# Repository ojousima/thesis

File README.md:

# Energy Harvester Design for Intelligent Tyre Systems
##TLDR
Modern tyres can have sensor systems which require energy. Currently these 
systems are powered by batteries, which limit the power available and lifetime
of the systems. This study presents an energy harvester system to power such
sensor systems. Piezoelectric and electromagnetic harvester designs are presented
and the piezoelectric harvester design was selected for use in the tyre. Electrical
energy was harvested from tyre rotation and deformation, harvested power was
rectified and stored into a supercapacitor at a voltage level usable by modern
microcontrollers. Tens of milliwatts of electrical power was obtained from both
harvesters in a vibration exciter test setup, and the piezoelectric harvester produced
13 microwatts of electrical power in a chassis dynamometer test rig. Further testing
indicates 50 microwatts of power is obtainable at a higher speed of the tyre. The
power obtained from harvester exceeds sleep mode power requirement of sensor
system, and the sensor system could be theoretically operated intermittently with
the power available from harvester. Continuous operation of a sensor system is not
feasible with the presented harvester.

##The Good Parts
Some of the energy harvesting hardware under folder "hardware" has sparked interest. Printed circuit boards are designed in open source software KiCAD which allows anyone to explore and modify designs without investing in expensive software licenses. 

PCB designs are licensed under CERN OHL 1.2, please see [LICENSE.md](/LICENSE.md) for details.

My personal favourite piece of work during the thesis was making animations of magnetic fields using a magnetics FEA software *FEMM*. Lua scripts were used to step parameters of the simulation and exporting images of fields strenghts. Finally *convert* was used to create animations from the images.
for example `convert -delay 12 -loop 0 magnet*.bmp animated.gif` .

Maybe the most interesting detail in the thesis is application of ferrofluid in electromagnetic harvester design. Ferrofluid significantly lowers the friction rotor magnet sees inside the shaft of generator, bringing a lot sharper peak in frequency output as seen in figure below.

.

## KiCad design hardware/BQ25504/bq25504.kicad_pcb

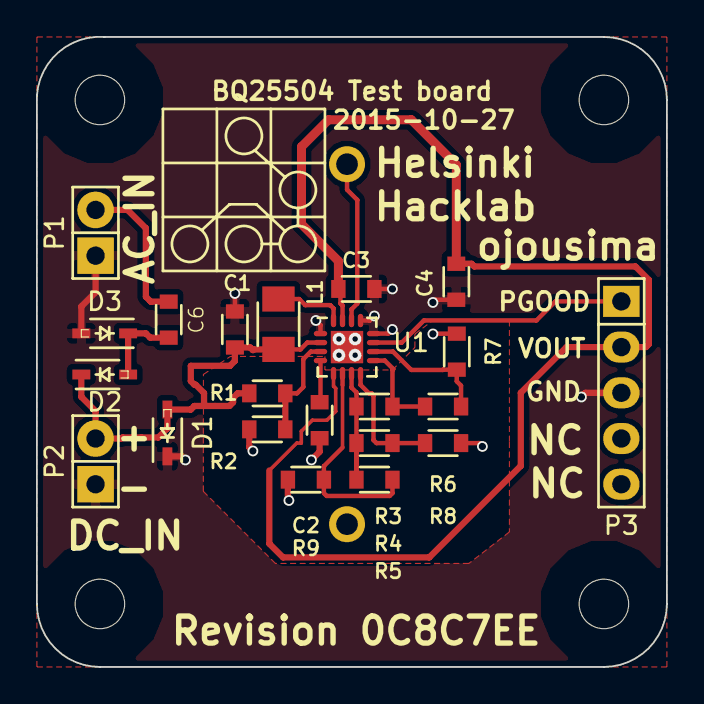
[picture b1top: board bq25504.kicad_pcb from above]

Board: 2 copper layers, 35.0 x 35.0 mm, 27 parts (1 on the bottom side), 15 nets.

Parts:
C1, C2, C3, C4, C6: C; SMD0603_A
C5: EECRG0V155(V|H)N; EECRG0V155HN
D1: TVS; SOD-323-A
D2, D3: D_Schottky; SOD-323-A
L1: INDUCTOR_SMALL; SMD1206_A
NC1, NC2, NC3, NC4: Mounting_hole; m2.5_mechanical_npth_mount
P1, P2: CONN_01X02; Pin_Header_Straight_1x02
P3: CONN_01X03; Pin_Header_Straight_1x05
R1, R2, R3, R4, R5, R6, R7, R8, R9: R_Small; SMD0603_A
U1: BQ25504; QFN-16-1EP_3x3mm_Pitch0.5mm

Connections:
/HYST: R3.2, R6.1, U1.9
/PROG: R6.2, R7.1, U1.10
/VBAT_OK: P3.1, U1.11
/VBOV: R5.2, R9.1, U1.6
/VBUV: R4.2, R8.1, U1.8
/V_IN: C1.1, D1.2, D2.1, L1.1, P2.2, R1.1, U1.2
/V_OC_SAMP: R1.2, R2.1, U1.3
/V_RDIV: R3.1, R4.1, R5.1, U1.7
/V_REF: C2.2, U1.4
/V_SYS: C3.1, C4.1, P3.2, U1.5, U1.15
GND: C1.2, C2.1, C3.2, C4.2, C5.2, D1.1, D3.2, P1.1, P2.1, P3.3, R2.2, R7.2, R8.2, R9.2, U1.1, U1.12, U1.13, U1.17
unnamed: C5.1, U1.14
unnamed: C6.1, D2.2, D3.1
unnamed: C6.2, P1.2
unnamed: L1.2, U1.16

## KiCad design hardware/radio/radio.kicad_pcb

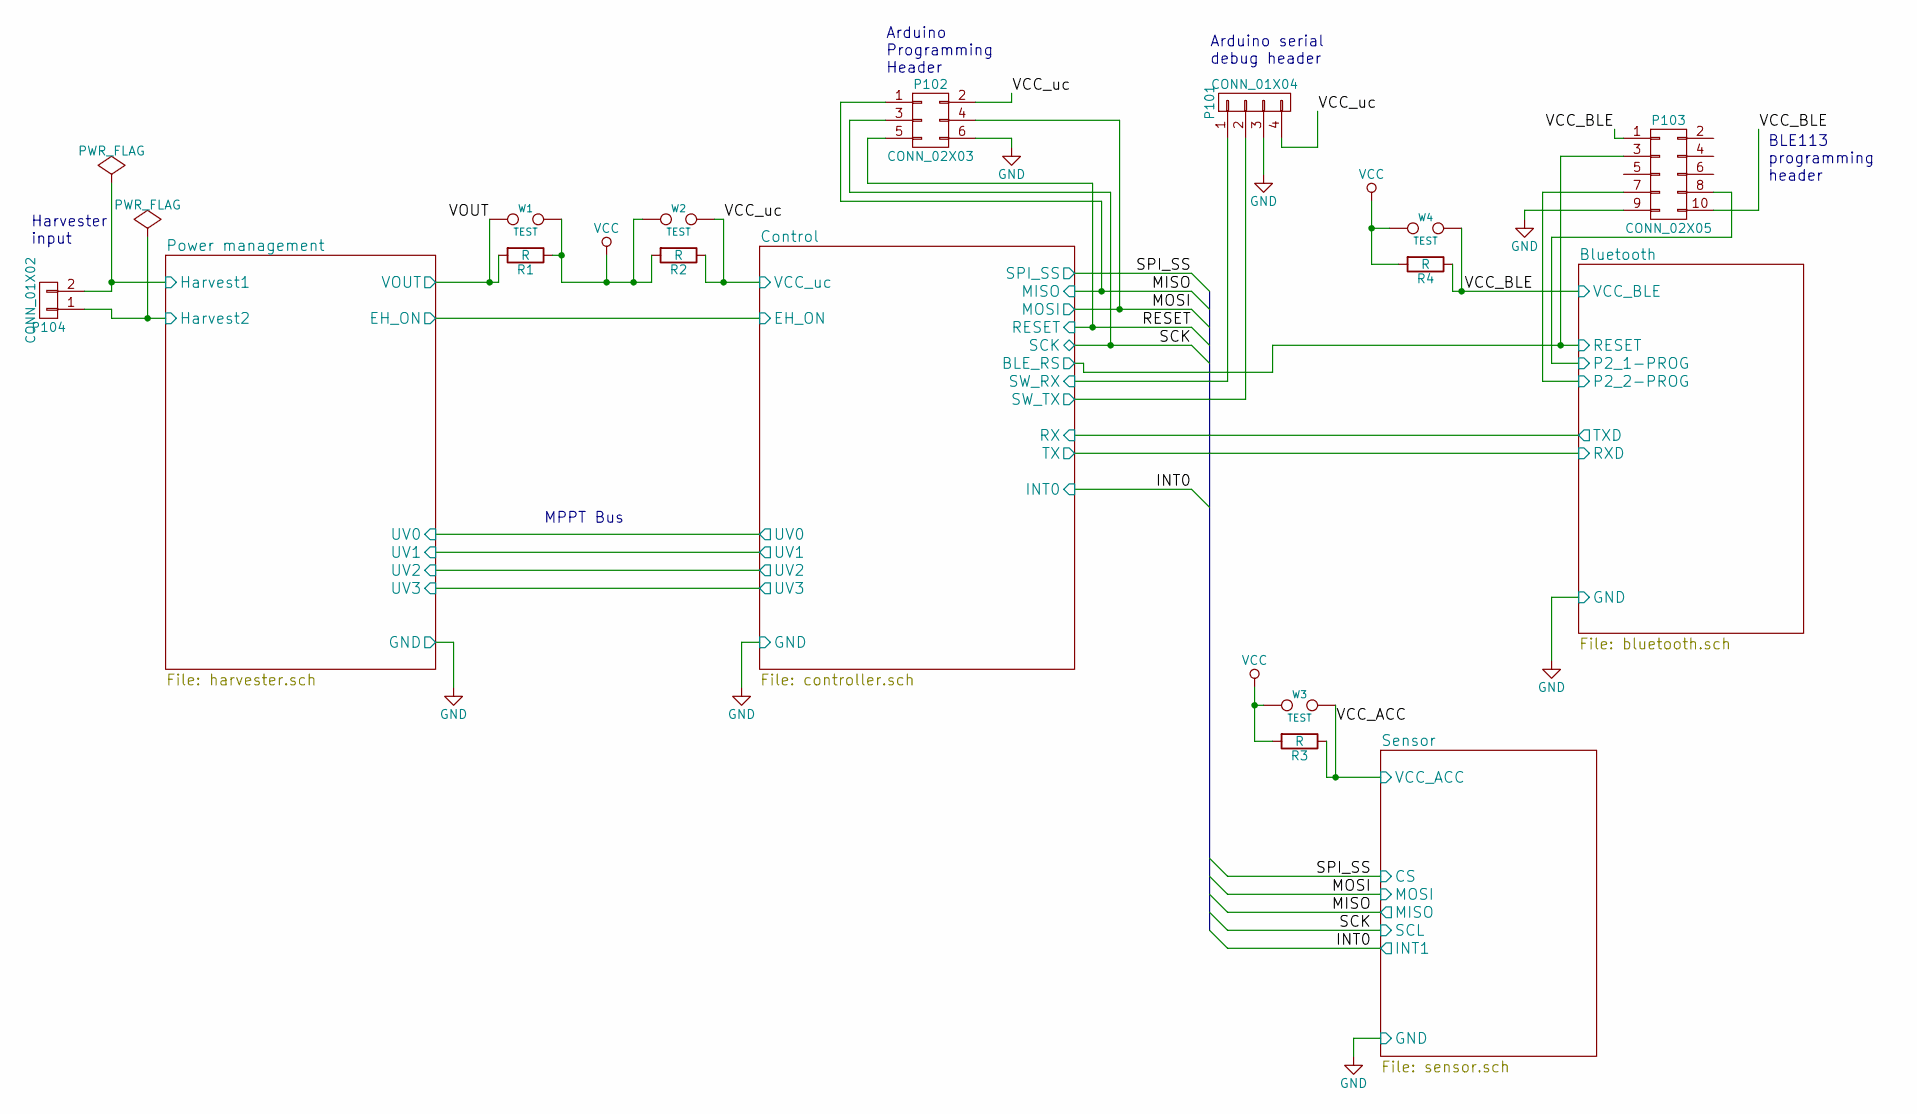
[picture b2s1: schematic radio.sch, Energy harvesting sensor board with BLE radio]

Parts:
P101: CONN_01X04; Pin_Header_Straight_1x04
P102: CONN_02X03; Pin_Header_Straight_2x03
P103: CONN_02X05; Pin_Header_Straight_2x05_Pitch1.27mm
P104: CONN_01X02; Pin_Header_Straight_1x02
R1, R2, R3, R4: R; R_0603
W1, W2, W3, W4: TEST; Test_pair_TH_small

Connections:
/Bluetooth/P2_1-PROG: P103.8; also elsewhere on the board
/Bluetooth/P2_2-PROG: P103.7; also elsewhere on the board
/Bluetooth/VCC_BLE: P103.1, P103.10, R4.1, W4.2; also elsewhere on the board
/Control/BLE_RS: P103.3; also elsewhere on the board
/Control/MISO: P102.1; also elsewhere on the board
/Control/MOSI: P102.4; also elsewhere on the board
/Control/RESET: P102.5; also elsewhere on the board
/Control/SCK: P102.3; also elsewhere on the board
/Control/SW_RX: P101.1; also elsewhere on the board
/Control/SW_TX: P101.2; also elsewhere on the board
/Control/VCC_uc: P101.4, P102.2, R2.1, W2.2; also elsewhere on the board
/Power management/Harvest1: P104.2; also elsewhere on the board
/Power management/Harvest2: P104.1; also elsewhere on the board
/Power management/VOUT: R1.2, W1.1; also elsewhere on the board
/Sensor/VCC_ACC: R3.1, W3.2; also elsewhere on the board
GND: P101.3, P102.6, P103.9; also elsewhere on the board
VCC: R1.1, R2.2, R3.2, R4.2, W1.2, W2.1, W3.1, W4.1

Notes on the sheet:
Harvester input
MPPT Bus
BLE113 programming header
Arduino Programming Header
Arduino serial debug header

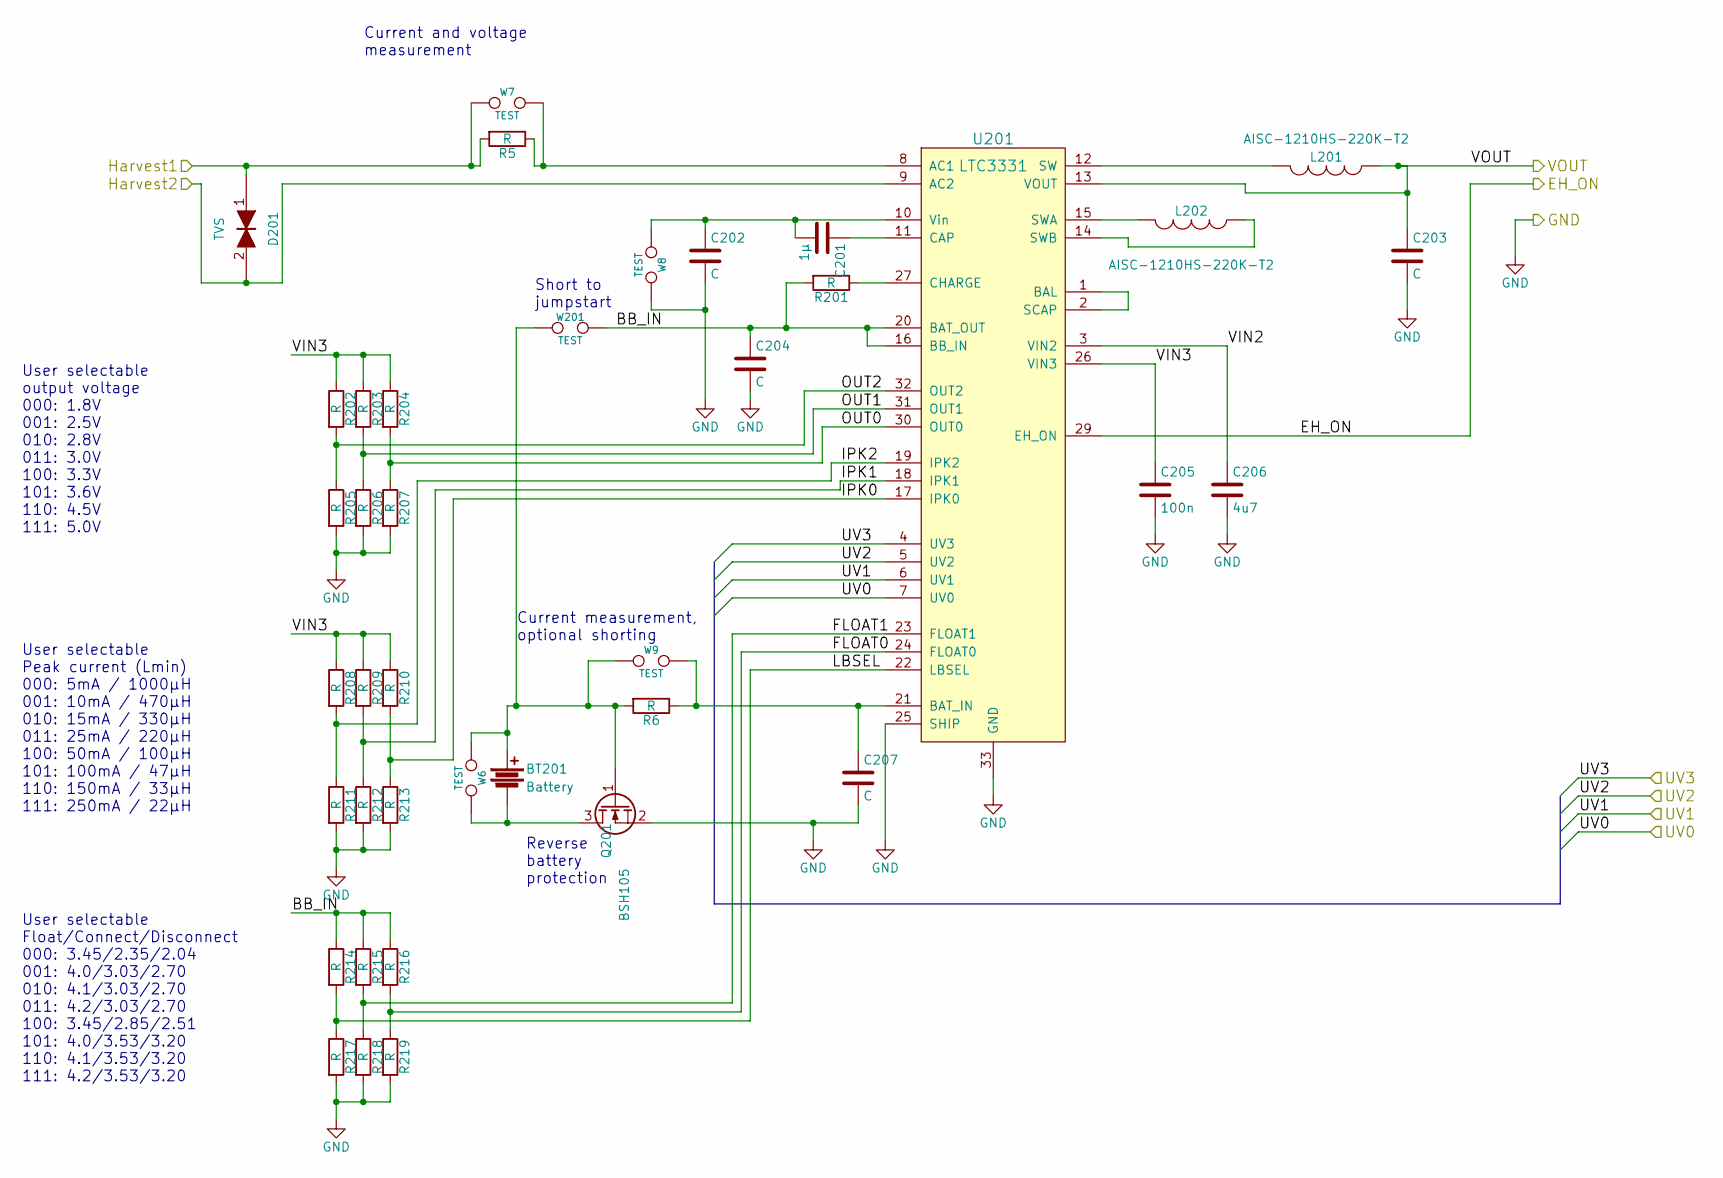
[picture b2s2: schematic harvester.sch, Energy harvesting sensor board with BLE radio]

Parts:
BT201: Battery; CR2032-holder-S8421R
C201: 1µ; C_0603
C202, C203, C204, C207: C; C_0603
C205: 100n; C_0603
C206: 4u7; C_0603
D201: TVS; SOD-323
L201, L202: AISC-1210HS-220K-T2; R_1210
Q201: BSH105
R5, R6, R201, R202, R203, R204, R205, R206, R207, R208, R209, R210, R211, R212, R213, R214, R215, R216, R217, R218, R219: R; R_0603
U201: LTC3331; QFN-32-1EP_5x5mm_Pitch0.5mm
W6, W8: TEST; Test_pair_TH_tiny
W7, W9, W201: TEST; Test_pair_TH_small

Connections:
/Control/EH_ON: U201.29 (EH_ON); also elsewhere on the board
/Control/UV0: U201.7 (UV0); also elsewhere on the board
/Control/UV1: U201.6 (UV1); also elsewhere on the board
/Control/UV2: U201.5 (UV2); also elsewhere on the board
/Control/UV3: U201.4 (UV3); also elsewhere on the board
/Power management/BB_IN: C204.1, R201.2, R214.1, R215.1, R216.1, U201.16 (BB_IN), U201.20 (BAT_OUT), W201.2
/Power management/FLOAT0: R216.2, R219.1, U201.24 (FLOAT0)
/Power management/FLOAT1: R215.2, R218.1, U201.23 (FLOAT1)
/Power management/Harvest1: D201.1, R5.2, W7.1; also elsewhere on the board
/Power management/Harvest2: D201.2, U201.9 (AC2); also elsewhere on the board
/Power management/IPK0: R210.2, R213.1, U201.17 (IPK0)
/Power management/IPK1: R209.2, R212.1, U201.18 (IPK1)
/Power management/IPK2: R208.2, R211.1, U201.19 (IPK2)
/Power management/LBSEL: R214.2, R217.1, U201.22 (LBSEL)
/Power management/OUT0: R204.2, R207.1, U201.30 (OUT0)
/Power management/OUT1: R203.2, R206.1, U201.31 (OUT1)
/Power management/OUT2: R202.2, R205.1, U201.32 (OUT2)
/Power management/VIN2: C206.1, U201.3 (VIN2)
/Power management/VIN3: C205.1, R202.1, R203.1, R204.1, R208.1, R209.1, R210.1, U201.26 (VIN3)
/Power management/VOUT: C203.1, L201.1, U201.13 (VOUT); also elsewhere on the board
GND: C202.2, C203.2, C204.2, C205.2, C206.2, C207.2, Q201.2 (S), R205.2, R206.2, R207.2, R211.2, R212.2, R213.2, R217.2, R218.2, R219.2, U201.25 (SHIP), U201.33 (GND), W8.2; also elsewhere on the board
unnamed: BT201.1, Q201.1 (G), R6.2, W6.1, W9.1, W201.1
unnamed: BT201.2, Q201.3 (D), W6.2
unnamed: C201.1, U201.11 (CAP)
unnamed: C201.2, C202.1, U201.10 (Vin), W8.1
unnamed: C207.1, R6.1, U201.21 (BAT_IN), W9.2
unnamed: L201.2, U201.12 (SW)
unnamed: L202.1, U201.14 (SWB)
unnamed: L202.2, U201.15 (SWA)
unnamed: R5.1, U201.8 (AC1), W7.2
unnamed: R201.1, U201.27 (CHARGE)
unnamed: U201.1 (BAL), U201.2 (SCAP)

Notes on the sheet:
User selectable output voltage 000: 1.8V 001: 2.5V 010: 2.8V 011: 3.0V 100: 3.3V 101: 3.6V 110: 4.5V 111: 5.0V
User selectable Float/Connect/Disconnect 000: 3.45/2.35/2.04 001: 4.0/3.03/2.70 010: 4.1/3.03/2.70 011: 4.2/3.03/2.70 100: 3.45/2.85/2.51 101: 4.0/3.53/3.20 110: 4.1/3.53/3.20 111: 4.2/3.53/3.20
User selectable Peak current (Lmin) 000: 5mA / 1000µH 001: 10mA / 470µH 010: 15mA / 330µH 011: 25mA / 220µH 100: 50mA / 100µH 101: 100mA / 47µH 110: 150mA / 33µH 111: 250mA / 22µH
Reverse battery protection
Current measurement, optional shorting
Current and voltage measurement
Short to jumpstart

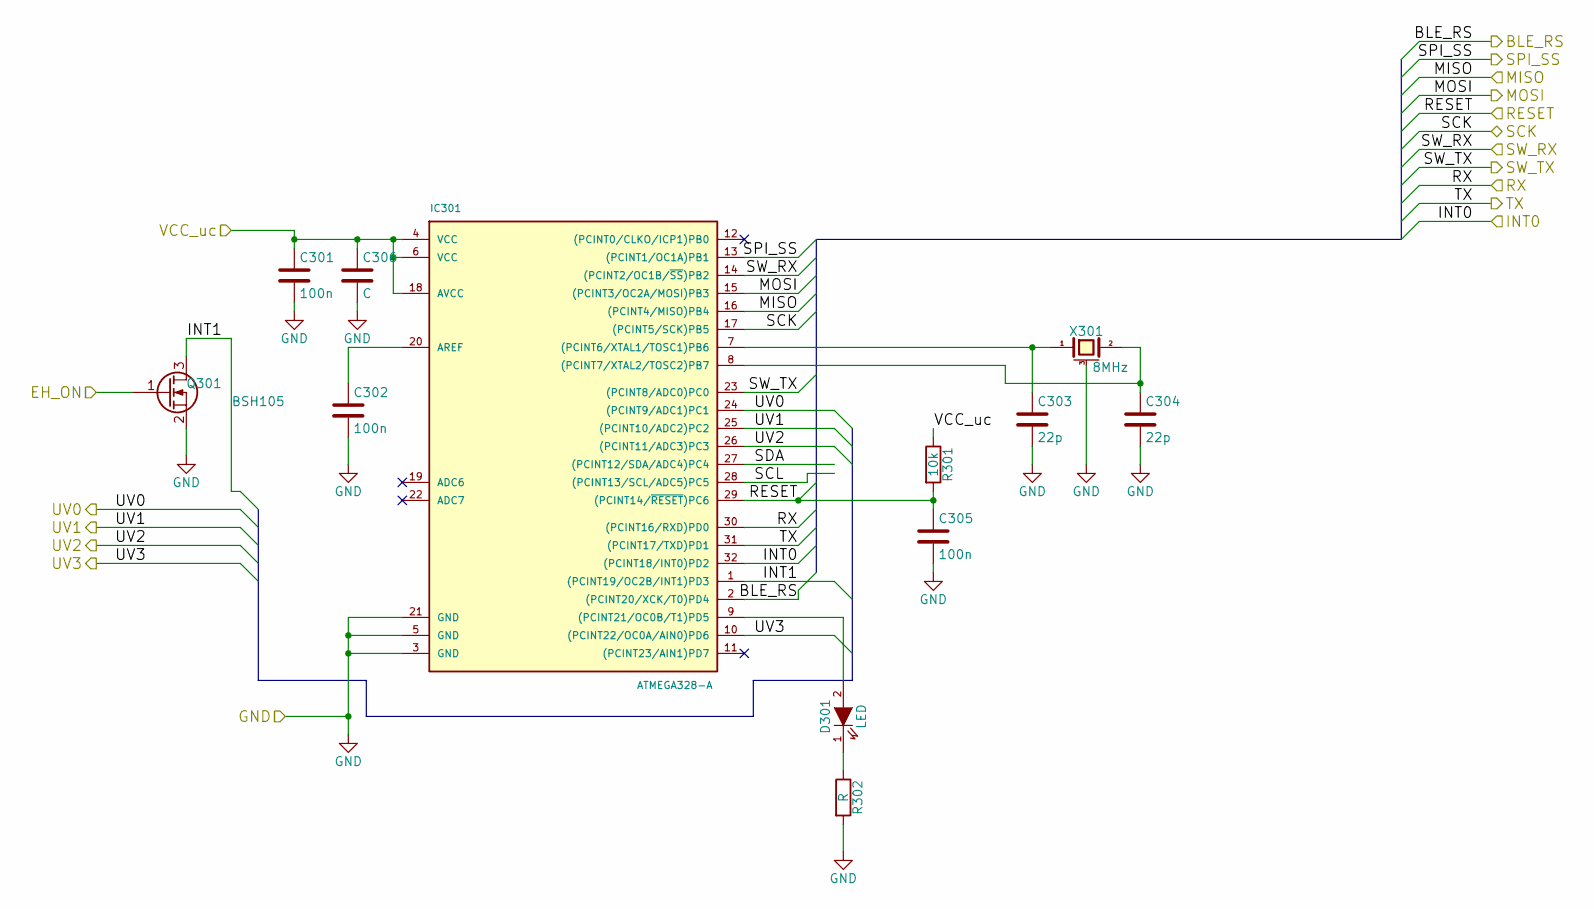
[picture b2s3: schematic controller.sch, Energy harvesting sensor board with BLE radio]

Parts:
C301, C302, C305: 100n; C_0603
C303, C304: 22p; C_0603
C306: C; C_0603
D301: LED; LED-0603
IC301: ATMEGA328-A; TQFP-32_7x7mm_Pitch0.8mm
Q301: BSH105
R301: 10k; R_0603
R302: R; R_0603
X301: 8MHz; crystal_FA238-TSX3225

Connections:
/Bluetooth/RXD: IC301.31 ((PCINT17/TXD)PD1); also elsewhere on the board
/Control/BLE_RS: IC301.2 ((PCINT20/XCK/T0)PD4); also elsewhere on the board
/Control/EH_ON: Q301.1 (G); also elsewhere on the board
/Control/INT0: IC301.32 ((PCINT18/INT0)PD2); also elsewhere on the board
/Control/INT1: IC301.1 ((PCINT19/OC2B/INT1)PD3), Q301.3 (D)
/Control/MISO: IC301.16 ((PCINT4/MISO)PB4); also elsewhere on the board
/Control/MOSI: IC301.15 ((PCINT3/OC2A/MOSI)PB3); also elsewhere on the board
/Control/RESET: C305.1, IC301.29 ((PCINT14/~RESET~)PC6), R301.2; also elsewhere on the board
/Control/RX: IC301.30 ((PCINT16/RXD)PD0); also elsewhere on the board
/Control/SCK: IC301.17 ((PCINT5/SCK)PB5); also elsewhere on the board
/Control/SCL: IC301.28 ((PCINT13/SCL/ADC5)PC5)
/Control/SDA: IC301.27 ((PCINT12/SDA/ADC4)PC4)
/Control/SW_RX: IC301.14 ((PCINT2/OC1B/~SS~)PB2); also elsewhere on the board
/Control/SW_TX: IC301.23 ((PCINT8/ADC0)PC0); also elsewhere on the board
/Control/UV0: IC301.24 ((PCINT9/ADC1)PC1); also elsewhere on the board
/Control/UV1: IC301.25 ((PCINT10/ADC2)PC2); also elsewhere on the board
/Control/UV2: IC301.26 ((PCINT11/ADC3)PC3); also elsewhere on the board
/Control/UV3: IC301.10 ((PCINT22/OC0A/AIN0)PD6); also elsewhere on the board
/Control/VCC_uc: C301.1, C306.1, IC301.4 (VCC), IC301.6 (VCC), IC301.18 (AVCC), R301.1; also elsewhere on the board
/Sensor/CS: IC301.13 ((PCINT1/OC1A)PB1); also elsewhere on the board
GND: C301.2, C302.2, C303.2, C304.2, C305.2, C306.2, IC301.3 (GND), IC301.5 (GND), IC301.21 (GND), Q301.2 (S), R302.2, X301.3 (case); also elsewhere on the board
unnamed: C302.1, IC301.20 (AREF)
unnamed: C303.1, IC301.7 ((PCINT6/XTAL1/TOSC1)PB6), X301.1
unnamed: C304.1, IC301.8 ((PCINT7/XTAL2/TOSC2)PB7), X301.2
unnamed: D301.1 (K), R302.1
unnamed: D301.2 (A), IC301.9 ((PCINT21/OC0B/T1)PD5)

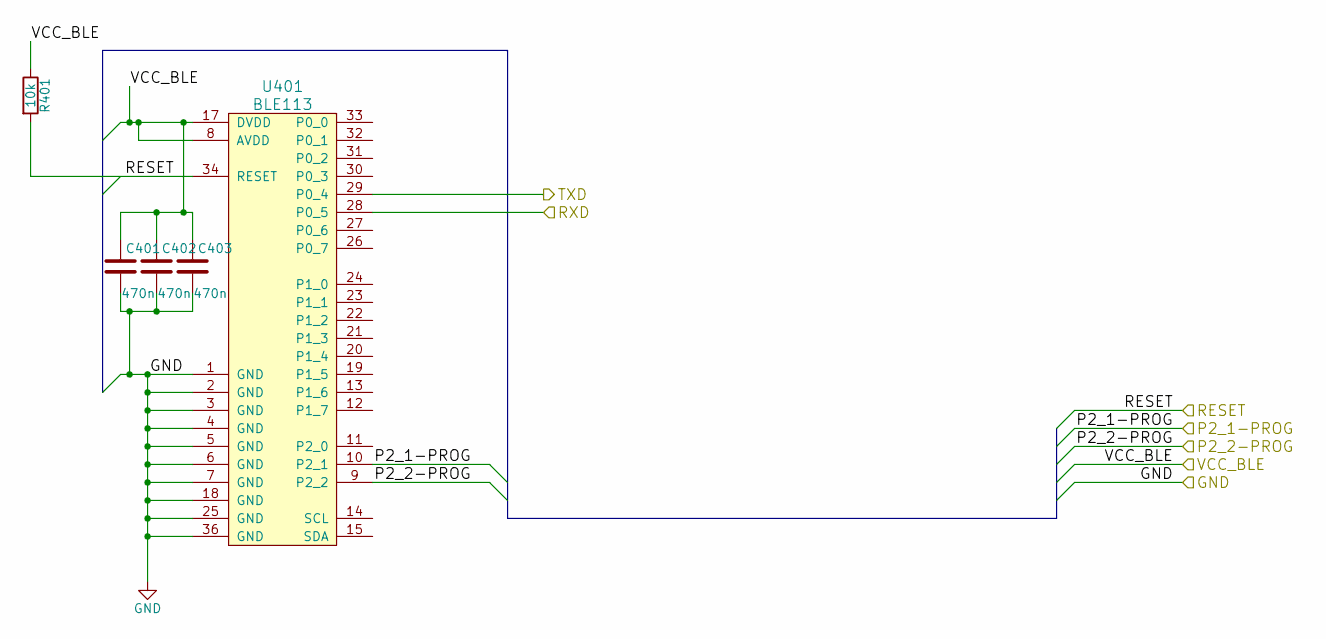
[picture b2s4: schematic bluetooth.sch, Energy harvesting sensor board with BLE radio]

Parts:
C401, C402, C403: 470n; C_0603
R401: 10k; R_0603
U401: BLE113

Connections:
/Bluetooth/P2_1-PROG: U401.10 (P2_1); also elsewhere on the board
/Bluetooth/P2_2-PROG: U401.9 (P2_2); also elsewhere on the board
/Bluetooth/RXD: U401.28 (P0_5); also elsewhere on the board
/Bluetooth/VCC_BLE: C401.1, C402.1, C403.1, R401.1, U401.8 (AVDD), U401.17 (DVDD); also elsewhere on the board
/Control/BLE_RS: R401.2, U401.34 (RESET); also elsewhere on the board
/Control/RX: U401.29 (P0_4); also elsewhere on the board
GND: C401.2, C402.2, C403.2, U401.1 (GND), U401.2 (GND), U401.3 (GND), U401.4 (GND), U401.5 (GND), U401.6 (GND), U401.7 (GND), U401.18 (GND), U401.25 (GND), U401.36 (GND); also elsewhere on the board

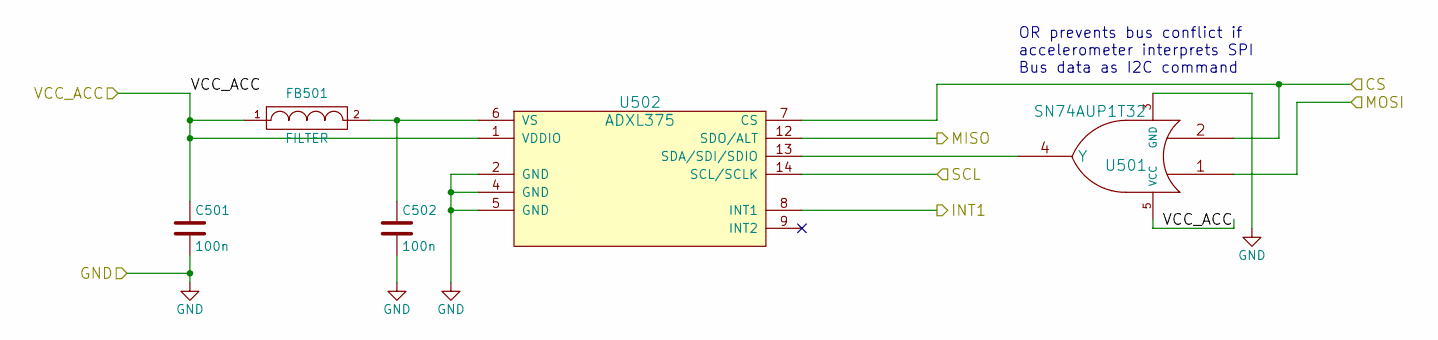
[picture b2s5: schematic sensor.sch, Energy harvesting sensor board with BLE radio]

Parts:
C501, C502: 100n; C_0603
FB501: FILTER; R_0603
U501: SN74AUP1T32; SOT-23-5
U502: ADXL375; LGA-14_(CC-14-1)

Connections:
/Control/INT0: U502.8 (INT1); also elsewhere on the board
/Control/MISO: U502.12 (SDO/ALT); also elsewhere on the board
/Control/MOSI: U501.1; also elsewhere on the board
/Control/SCK: U502.14 (SCL/SCLK); also elsewhere on the board
/Sensor/CS: U501.2, U502.7 (CS); also elsewhere on the board
/Sensor/VCC_ACC: C501.1, FB501.1, U501.5 (VCC), U502.1 (VDDIO); also elsewhere on the board
GND: C501.2, C502.2, U501.3 (GND), U502.2 (GND), U502.4 (GND), U502.5 (GND); also elsewhere on the board
unnamed: C502.1, FB501.2, U502.6 (VS)
unnamed: U501.4 (Y), U502.13 (SDA/SDI/SDIO)

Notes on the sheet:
OR prevents bus conflict if accelerometer interprets SPI Bus data as I2C command

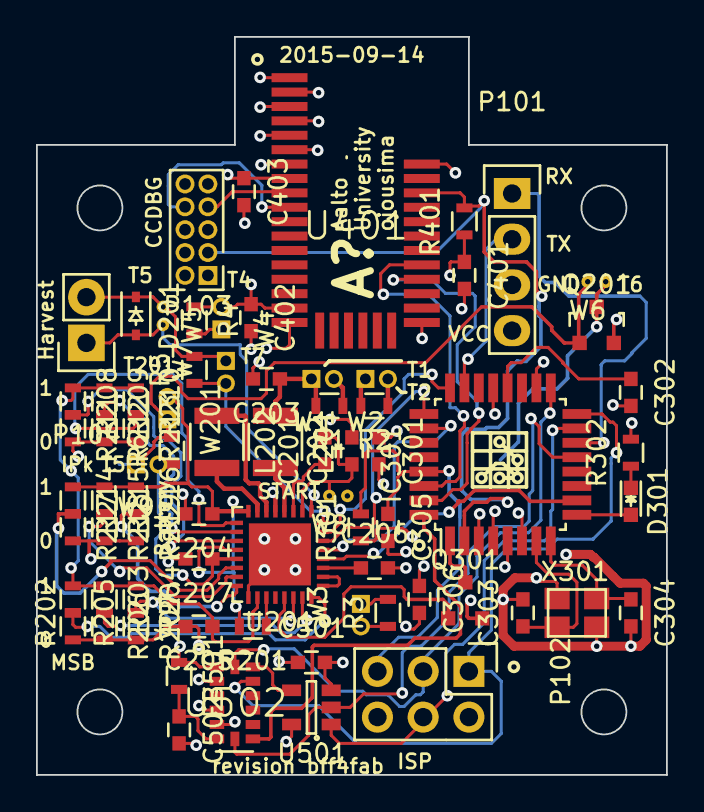
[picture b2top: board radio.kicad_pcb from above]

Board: 4 copper layers, 35.0 x 41.0 mm, 74 parts (1 on the bottom side), 57 nets.

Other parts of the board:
W5: TEST; Test_pair_TH_tiny

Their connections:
/Power management/Harvest1: W5.2; also elsewhere on the board
/Power management/Harvest2: W5.1; also elsewhere on the board

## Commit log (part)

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2015-08-20 Add force vs distance calculations, images
2015-08-20 Add text about FEA analysis of magnetic forces
2015-08-20 Add picture of tyre
2015-08-20 Fix typo in image name
2015-08-21 Add chapter about structure of tyre
2015-08-21 Fix typos, formatting of design
2015-08-24 Add text on flux linkage
2015-08-24 update compiled thesis
2015-08-24 Add image of LTSpice model
2015-08-24 Add simulation data of flux linkage
2015-08-25 update graphical look of LTSpice sim
2015-08-31 Update design text
2015-08-31 Add piezo test results and pictures of test setups
2015-08-31 Add Piexo MPPT schematic
2015-08-31 Add datasheet of ceramic vs tantalum reliability
2015-09-01 Add signaling LEDs to voltage clamps, adjust time constant on peak detect.
2015-09-01 Add piezo measurement simulation
2015-09-03 Add MPPT schematic capture
2015-09-05 Reduce complexity of MPPT schematic
2015-09-05 Tune LTSpice simulation
2015-09-05 Add system schematics.
2015-09-05 Set simulation magnet to correct spot
2015-09-05 Associate footprints
2015-09-05 Draw PCB outline
2015-09-05 Add ATMEGA328 footprint
2015-09-05 Add radio footprint to PCB
2015-09-06 Add accelerometer to schematic
2015-09-06 Add footprints for BLE113, battery, accelerometer
2015-09-06 Add KiCAD -bak files to gitignore
2015-09-06 Add _saved_ files to gitignore
2015-09-06 Remove kicad backup file from version control
2015-09-06 Associate battery, BLE113, OR-gate, ADXL375 footprints
2015-09-07 Work on PCB
2015-09-07 Add OpenSCAD model of system stack
2015-09-08 Start routing the PCB
2015-09-08 Fix the µC part number, pin numbering
2015-09-08 Add KiCAD .bak -files to gitignore
2015-09-08 Add page descriptions to schematics
2015-09-08 remove .bak files from version control
2015-09-08 Add printout of schematic
2015-09-11 Add test points for current and voltage
2015-09-13 Assign testpoint footprints
2015-09-13 Work on laying out TPs
2015-09-13 Continue on TP layout
2015-09-13 Give sensor own power net
2015-09-13 Create test point footprints
2015-09-13 Assign Q1 footprint
2015-09-13 Fix merge conflict on kicad-pcb
2015-09-13 Save before removing test points
2015-09-13 Parts placed
2015-09-13 Work on layout
2015-09-13 Change inductor footprints to 1210
2015-09-13 Routing finalized
2015-09-13 Add revision information
2015-09-13 Shrink mounting holes to 2.5mm dia
2015-09-14 Add text on schematic design
2015-09-14 Add printout of bluetooth schematic
2015-09-14 Add text on circuit board layout
2015-09-14 compress schematic for embedding images in thesis
2015-09-16 Compress schematics for printouts
2015-09-16 Add measurement data from LPMG on shaker
2015-09-16 Make script now removes old thesis
2015-09-16 Add images of schematic and circuit
2015-09-16 Add printout of thesis
2015-09-16 Start work on laser cut pieces of generators
2015-09-17 Ignore gerber output
2015-09-17 Ignore KiCAD autosave file
2015-09-17 Ignore drill file
2015-09-17 Mechanical cuts for 10X15cm plate done
2015-09-17 Add descriptions of shapes to cutout image
2015-09-18 Write about piezos in background
2015-09-18 Select image from piezo test to use
2015-09-18 Text on piezos, background
2015-09-18 Fix Latex issues
2015-09-18 work on design
2015-09-18 Regenerate library
2015-09-18 Fix latex errors
2015-09-18 Fix Typos
2015-09-22 Add active rectification circuit with boost
2015-09-28 Add magcode as submodule
2015-09-28 Add matlab/SIMULINK block models
2015-09-28 Add screen capture of LG scope view
2015-09-28 Add raw gimp files to version control
2015-10-07 Combine model
2015-10-07 Add notice of origin of acceleration data
2015-10-08 Add captures of matlab simulation of PMLG
2015-10-12 Added images of measurement data
2015-10-12 add images
2015-10-12 Update compiled library, thesis
2015-10-12 Fix pathname of lg_proto.jpg
2015-10-14 Update piezo model
2015-10-14 Add graphs of measurement
2015-10-14 Removed minamed file
2015-10-14 Restore accidentally deleted measurement data
2015-10-14 Add axes, combine accelerometer data figures
2015-10-15 Compress schematics for screenshots
2015-10-15 Add BoM
2015-10-15 Fix centrifugal force calculation
2015-10-15 Edit images on background and design
2015-10-15 Remove commented out section on background
2015-10-15 Refine text on background
2015-10-15 Tune piezo model
2015-10-15 Automatically open pdf after compiling
2015-10-15 ADD LTSpice simulation images
2015-10-15 Flatten image
2015-10-15 First draft of seminar text
2015-10-15 work on text
2015-10-15 Second draft of seminar text
2015-10-15 Update simulink images
2015-10-15 Add simulink screenshots
2015-10-15 Third revision of seminar text
2015-10-15 Proofread
2015-10-15 Update compiled seminar presentation
2015-10-15 Final adjustments
2015-10-15 Fix numbering issue
2015-10-28 update printout
2015-10-28 Update openscad model
2015-10-28 Add simulink waveforms
2015-11-09 Add MPPT to block diagram
2015-11-25 Add pictures of designs
2015-11-25 Add LTSpice simulation of voltage doubler
2015-11-25 Add desktop measurements
2015-11-25 Clarify images
2015-11-25 Remove template images
2015-11-25 Ignore various computer generated files
2015-11-25 Update kicad project file
2015-11-25 Update bibtex library
2015-11-26 Ignore image thumbnails
2015-11-30 Add software to simulate discharge by radio, remove extra '.ino' from paths
2015-11-30 Add arduino software for testing BQ25504, levels based on PGOOD
2015-12-11 Add MPPT software for harvester
2015-12-11 Ignore various Atmel Studio autogenerated files
2015-12-12 Add images of generator, fix citations
2015-12-14 Move impact measeurement images
2015-12-14 Add images of shaker setup
2015-12-14 Add images of shaker test measurements
2015-12-14 Rename images
2015-12-17 Add raw labview-data from measurements
2015-12-17 Add images of PCB mounted in tyre
2015-12-17 write about mechanical design of EM harvester
2016-01-05 Add text on results
2016-01-11 Add piezo measurements
2016-01-11 Fix file types
2016-01-11 Add text
2016-01-11 Sort references by appearance
2016-01-11 Fix cosmetic issues
2016-01-11 Fix issue #6
2016-01-11 squash me
2016-01-12 Fix filenames
2016-01-17 Add measurement results
2016-01-17 Reorganize text as per feedback
2016-01-17 Finish TD results of PEH
2016-01-17 Comment LaTEX include
2016-01-17 Add text on PEH FD results
2016-01-17 Rename, adjust images
2016-01-17 Label section
2016-01-17 Add section on circuit design
2016-01-18 Adjust images for print
2016-01-18 Add text on harvesting circuit electrical performance
2016-01-18 Add text on dynometer results
2016-01-18 Add images, fix latex issues
2016-01-18 Remove .jpg for sharper .pdf
2016-01-18 Add updated thesis
2016-01-18 Add BQ25504 design files
2016-02-04 Add abstract, preface
2016-02-07 Remove magnetostrictive from tech to explore in detail
2016-02-07 Open acronym
2016-02-07 Fix #9
2016-02-08 Swap frequency- and timedomain results
2016-02-10 Add .gitattributes
2016-02-10 sync files after adding .gitaatributes
2016-02-25 Fix various issues
2016-02-25 Fix missing image
2016-02-25 squash
2016-02-25 Fix issues pointed out by Jaga sans pics
2016-02-25 Fix design, results as per Jaga's recommendations
2016-02-25 Image swaps, textual corrections as suggested by Yi
2016-02-25 Add state of art comparison, conclusion
2016-02-29 Ad conclusions, state of art results
2016-02-29 Add .lib files
2016-03-01 Crop images
2016-03-01 Ignore .dcm files
2016-03-02 Cosmetic touchup
2016-03-02 Fix references in thesis, cosmetic touch-ups
2016-03-03 Cosmetic improvements
2016-03-04 Improve references
2016-03-07 Fixes as per Tero's comments
2016-03-07 Fix latex errors, references
2016-03-07 Fix Visala's comments, proofread
2016-03-07 Fix typo
2016-03-08 Fix formatting, typo
2016-03-08 Update compiled version
2016-03-14 remove files which cannot be reproduced, add license, readme
2016-03-14 Fix README formatting
2016-03-14 Fix typo in readme
2016-03-14 Add text on FEMM simulation animations on README
2016-03-14 Clarify README
2016-04-11 Add animation of final harvester flux linkage simulation
